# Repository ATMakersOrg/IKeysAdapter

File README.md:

# IKeysAdapter
This is the hardware and software necessary to convert an IntelliKeys Keyboard to work as a standard HID device.

Software is licensed under an MIT License.  Hardware is Creative Commons S.A.

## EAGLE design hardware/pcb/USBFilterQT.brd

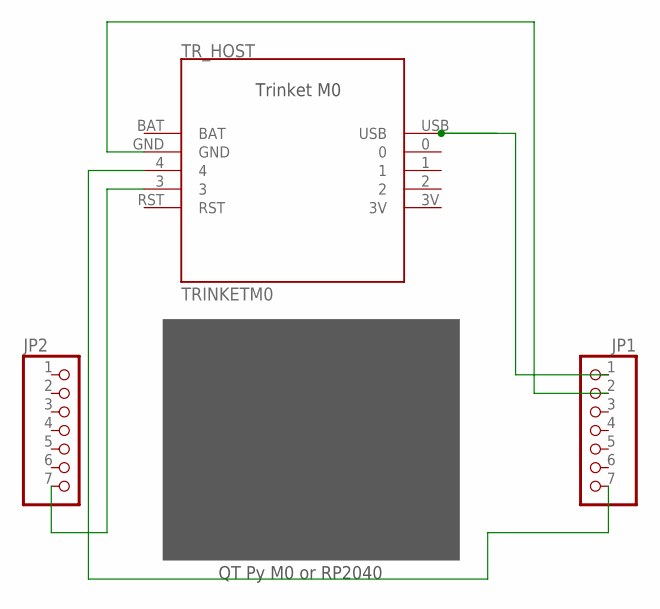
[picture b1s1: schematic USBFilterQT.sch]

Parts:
JP1, JP2: PINHD-1X7; 1X07
TR_HOST: TRINKETM0; TRINKET

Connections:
GND: JP1.2, TR_HOST.GND
unnamed: JP2.7, TR_HOST.3
unnamed: JP1.7, TR_HOST.4
USB: JP1.1, TR_HOST.USB

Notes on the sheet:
QT Py M0 or RP2040

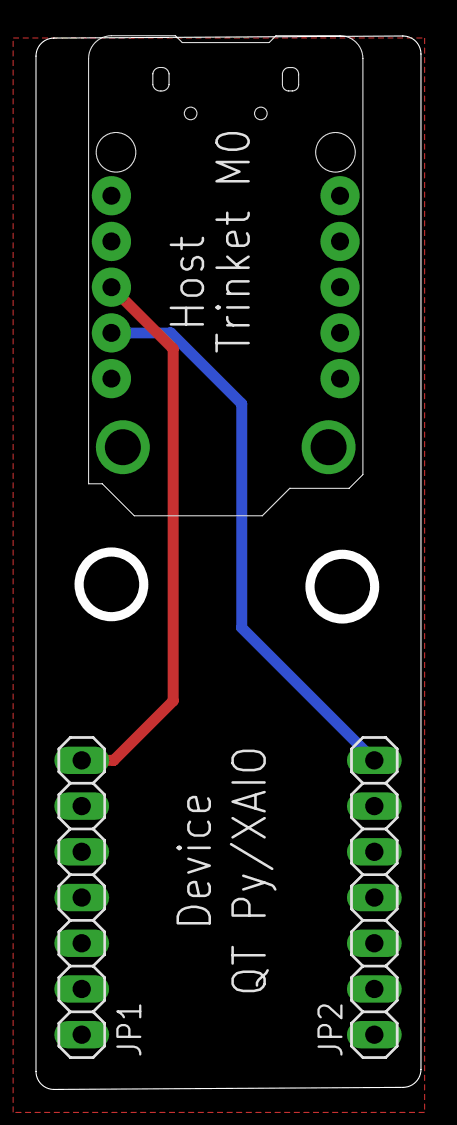
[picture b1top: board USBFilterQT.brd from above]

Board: 2 copper layers, 21.4 x 58.5 mm, 3 parts (0 on the bottom side), 4 nets.

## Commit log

2020-01-25 Initial upload
    This has code for the PC and Mac Versions as well as the Arduino .ino file. Lots more to add to make this usable. Contact bill@atmakers.org if you need help at this point.
2020-02-11 Adding XBox
2020-02-11 Restructured and added Mac and harward
2022-06-07 AddingQT files and UF2 for host side
